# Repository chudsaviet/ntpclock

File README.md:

NTP synchronized desktop 7-segment clock
=======================================================
Features
--------
1. **NTP** sunchronization using WiFi.
2. **RTC** backup - will show time from a high precision RTC if WiFi is not available.
3. Automatic display **brightness** control.
4. Automatic **timezone** data update from online TZDATA database.
5. Settings via WiFi AP mode and a web page.

Pictures
--------

Bill of materials
-----------------

| Part                            | Price |
| ------------------------------- | ------|
| ESP32, Generic DevKit V1        | $8    |
| Adafruit 1.2" 7-segment display | $18   |
| DS3231*SN* RTC module           | $18   |
| Adafruit VEML7700 lux sensor    | $5    |
| Custom I2C and power hub board  | $5    |
| Jumper wires, Female-Female     | $2    |
| M3, M2.5 and M2 bolts           | $5    |
| 3D printed plastic enclosure    | $8    |
| Tint film (ex. for cars)        | $1    |
| ------------------------------- | ----- |
| Total                           | $70   |

Building and running the device
-------------------------------
1. Manufacture I2C/Power hub using files from `cad/i2c_header_x5`. Don't forget 3.2K pull-up resistors.
2. 3D print enclosure using files from `cad/enclosure`.
3. Apply tint film to the display module.
4. **Assemble the device.** Select appropriate screw diameter and length for each hole. Connect hub 5V to VIN in ESP32, ground to ground, 3.3V to 3.3V, SDA/SCL to appropriate ESP32 pins. Connect every component to the hub.
5. Install ESP-IDF **v4.4** - https://github.com/espressif/esp-idf/tree/release/v4.4 .
6. Clone repository and **init submodules recursively**.
7. Copy `main/secrets.h` from `main/secrets.h.example` and set your own setting inside.
8. Using instructions from EPS-IDF, build and flash the firmware.

Changing settings after flashing firmware
-----------------------------------------
1. To change settings after flash, connect the device to power and press 'SET' button on the bottom.
2. Device will create a WiFi AP with SSID looking like `ntpclock-XXXXXXXX`.
3. The password will be shown scrolling on display.
4. Connect to AP and open http://192.168.4.1 .

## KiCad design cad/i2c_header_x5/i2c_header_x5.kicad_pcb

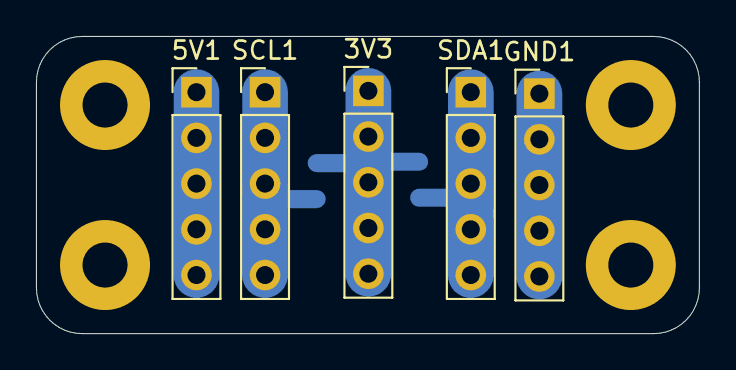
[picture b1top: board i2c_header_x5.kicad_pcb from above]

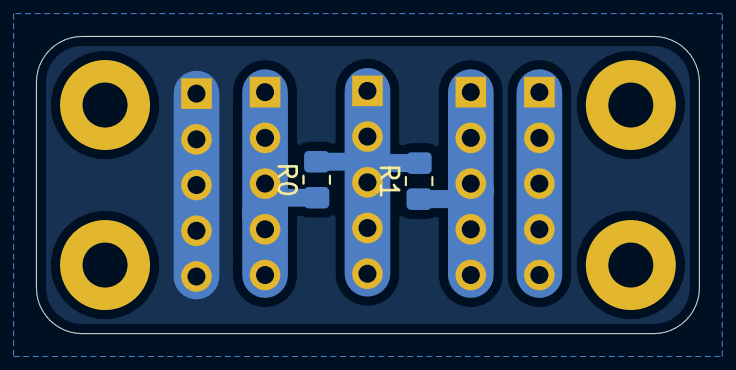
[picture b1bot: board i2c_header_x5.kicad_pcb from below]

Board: 2 copper layers, 36.8 x 16.5 mm, 7 parts (2 on the bottom side), 5 nets.

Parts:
3V3, 5V1: Conn_01x05_Male; PinHeader_1x05_P2.54mm_Vertical
GND1: Conn_01x05_Male; PinHeader_1x05_P2.54mm_Vertical
R0, R1: 4K7; R_0805_2012Metric_Pad1.20x1.40mm_HandSolder
SCL1: Conn_01x05_Male; PinHeader_1x05_P2.54mm_Vertical
SDA1: Conn_01x05_Male; PinHeader_1x05_P2.54mm_Vertical

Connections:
unnamed: 3V3.1, 3V3.2, 3V3.3, 3V3.4, 3V3.5, R0.2, R1.2
unnamed: 5V1.1, 5V1.2, 5V1.3, 5V1.4, 5V1.5
unnamed: GND1.1, GND1.2, GND1.3, GND1.4, GND1.5
unnamed: R0.1, SDA1.1, SDA1.2, SDA1.3, SDA1.4, SDA1.5
unnamed: R1.1, SCL1.1, SCL1.2, SCL1.3, SCL1.4, SCL1.5

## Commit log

2021-08-23 Initial PlatformIO project.
2021-08-23 Added required libraries.
2021-08-23 Added NTPClient library. Written code to connect WiFi and get NTP time every 10 seconds.
2021-08-28 Added Time and TimeZoneInfo libraries. Prototyped timezone conversion.
2021-08-28 Made time to be displayed on the screen.
2021-08-29 Ticking using hardware timer.
2021-08-30 Added support for sub-second precision.
2021-08-30 Integrated NTP and RTC sync.
2021-08-30 Implemented more reasonable RTC/NTP switchover.
2021-09-01 Showing colons only if last sync was over NTP.
2021-09-04 Added WiFi reconnection on NTP sync failure.
2021-09-06 Moved headers to directory.
2021-09-06 Added lux sensor code.
2021-09-28 Mitigated millis() overflow.
2021-10-13 Moved display update from interrupt to main loop to avoid I2C race conditions.
2021-10-14 Updated WiFiNINA. Added wait for WiFi up when waking up from low power mode. Resolving NTP server name every time.
2021-10-19 Switched to esp32.
2021-10-24 Removec WiFi low power functions. WiFi power saving is done automatically in ESP32.
2021-10-31 Removed all NTPClient code.
2021-10-31 Switched to esp-idf time keeping and SNTP client.
2021-11-01 Implemented last NTP sync tracking and RTC backoff.
2021-11-01 Updating RTC on NTP sync.
2021-11-01 Bring back colons indication.
2021-11-01 Fixed timezone conversion issues.
2021-11-01 Fixed ALS issues.
2021-11-04 Added i2c semaphore. Increased NTP sync timeout to 4h.
2021-11-06 Moved ALS and display uppdate to a separate FreeRTOS task.
2021-11-18 Added CAD files (export from Fusion360).
2021-11-19 Created basic README.
2021-11-19 Moved enclosure CAD files to cad/enclosure.
2021-11-19 Added i2c_header_x5 KiCad PCB project.
2021-11-19 Updates README.md .
2021-11-29 Migrated to ESP-IDF and Arduino as ESP-IDF component.
2021-12-01 Switched to ESP-IDF native app_main() and native WiFi API.
2021-12-01 Added SMD pull-up resistors to i2c header.
2021-12-06 Moved WiFi control to a separate task. Implemented reconnection in case of failure.
2021-12-12 Added SPIFFS partition.
2021-12-13 Added unique ID code. Created delayed abort function.
2021-12-13 Enclosure refinements. v127
2021-12-14 Added button tracking using esp32-button component.
2021-12-14 Fixed button labels.
2021-12-15 Setting unique hostname. Created WPA key generation code.
2021-12-20 Tuned esp-idf build settings.
2021-12-21 Implemented communicatio using queues. Moved ALS to a task.
2021-12-21 Moved NTP watching to a task, using queue to pass events.
2021-12-22 Moved RTC operation to task and queue.
2021-12-23 Made display show scrolling WPA password.
2021-12-27 Starting AP mode when SET button pressed.
2021-12-27 Started webserver implementation.
2021-12-27 Created file server based on ESP-IDF example.
2021-12-29 Added basic HTTP API requests handling.
2021-12-29 Implemented first PUT request handler with JSON parsing.
2021-12-30 Keeping WiFi STA SSID and password in NVS. Implemented WiFi STA SSID and password REST API calls.
2021-12-30 Keeping .vscode/c_cpp_properties.json in the repository.
2021-12-30 Implemented HTTP file server serving files from SPIFFS.
2021-12-31 Created simple configuration page.
2021-12-31 Implemented setting SSID and password via web interface.
2022-01-02 Preparation to automatic www-data compression - copying it to build using custom command.
2022-01-02 Pre-compressing web content with GZip.
2022-01-06 Created initial web UI with Semantic (Formantic) UI.
2022-01-06 Removed unused font files.
2022-01-09 Using AP+STA mode instead of AP-only. Implemented WiFi scan API call.
2022-01-10 Implemented WiFi scanning in UI.
2022-01-10 Updated UI behavior.
2022-01-11 Added working Set button to SSID list.
2022-01-14 Implemented timezone control.
2022-01-14 Created timezone GET and PUT API.
2022-01-16 Added Time UI tab.
2022-01-16 Added NTP server API endpoint.
2022-01-18 Updated enclosure design to v139.
2022-01-19 Reworked NVS interaction.
2022-01-19 Timezone autoupdate famework finished.
2022-01-19 Fixed bug with Timezone dropdown set.
2022-01-19 Added timezone setting and automated update (#3)
    Added timezone setting and automated update
2022-01-19 Fix for displaying time after midnight
2022-01-19 Fix for displaying time after midnight (#4)
2022-01-25 Updated pictures in README.md .
2022-01-25 Replaced front render with real picture.
